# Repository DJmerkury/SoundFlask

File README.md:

# SoundFlask
Eurorack Modular Synthesizer Projects

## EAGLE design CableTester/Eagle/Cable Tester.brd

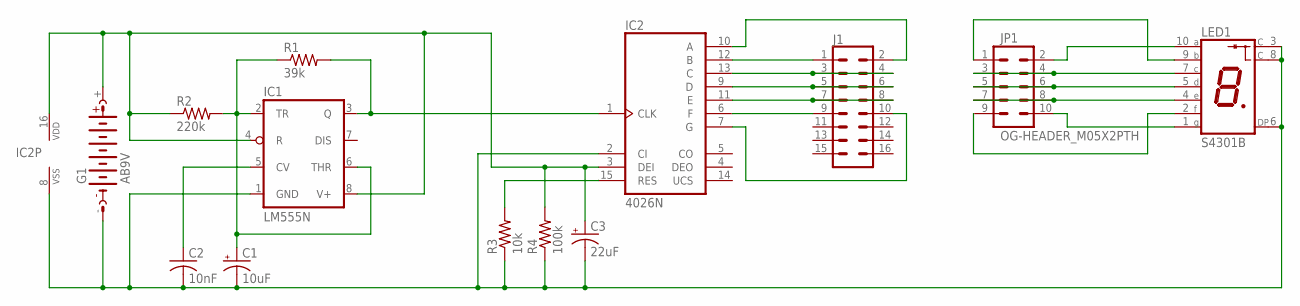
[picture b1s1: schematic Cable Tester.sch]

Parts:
C1: 10uF; RCL_E5-5
C2: 10nF; RCL_C050-055X075
C3: 22uF; RCL_E5-5
G1: AB9V
IC1: LM555N; DIL08
IC2: 4026N; DIL16
J1: CONN_08X2_HEADER; 2X8
JP1: OG-HEADER_M05X2PTH; OG-HEADER_AVR_ICSP
LED1: S4301B
R1: 39k; RESISTOR_0309/10
R2: 220k; RESISTOR_0309/10
R3: 10k; RESISTOR_0309/10
R4: 100k; RESISTOR_0309/10

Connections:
unnamed: C1.+, IC1.2 (TR), IC1.6 (THR), R1.1, R2.2
unnamed: IC1.3 (Q), IC2.1 (CLK), R1.2
unnamed: C2.1, IC1.5 (CV)
unnamed: IC2.15 (RES), R3.2
unnamed: IC2.10 (A), J1.2
unnamed: IC2.12 (B), J1.1
unnamed: IC2.13 (C), J1.3, J1.4
unnamed: IC2.9 (D), J1.5, J1.6
unnamed: IC2.11 (E), J1.7, J1.8
unnamed: IC2.6 (F), J1.9
unnamed: IC2.7 (G), J1.10
unnamed: JP1.2, LED1.10 (A)
unnamed: JP1.1, LED1.9 (B)
unnamed: JP1.3, JP1.4, LED1.7 (C)
unnamed: JP1.5, JP1.6, LED1.5 (D)
unnamed: JP1.7, JP1.8, LED1.4 (E)
unnamed: JP1.10, LED1.1 (G)
unnamed: JP1.9, LED1.2 (F)
unnamed: C3.+, G1.+, IC1.4 (R), IC1.8 (V+), IC2.3 (DEI), IC2.16 (VDD), R2.1, R4.2
unnamed: C1.-, C2.2, C3.-, G1.-, IC1.1 (GND), IC2.2 (CI), IC2.8 (VSS), LED1.3 (C), LED1.6 (DP), LED1.8 (C), R3.1, R4.1

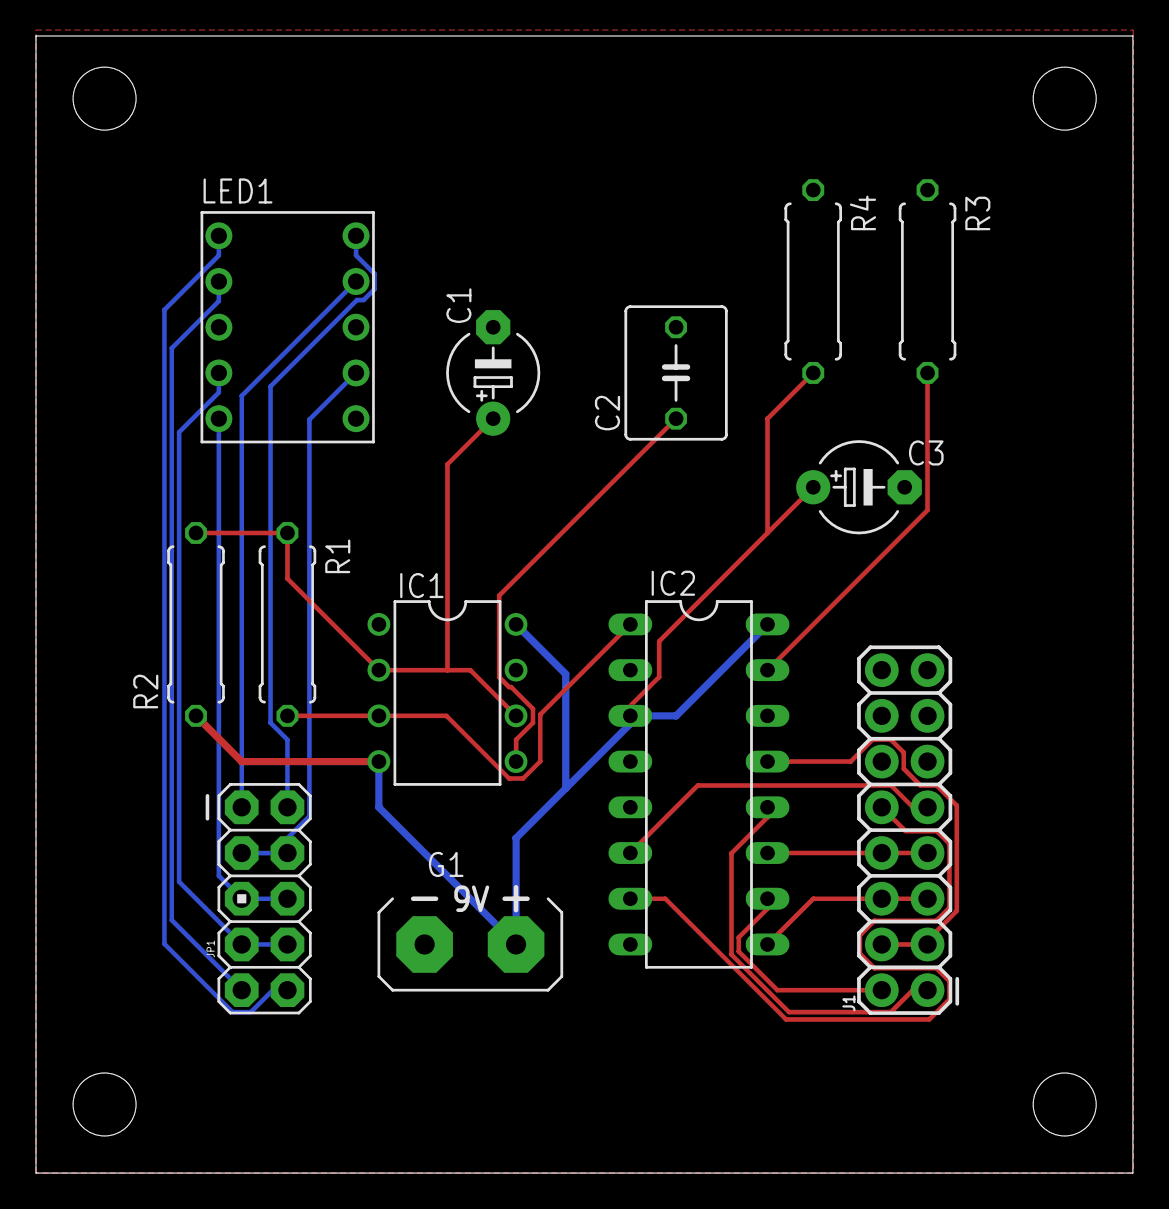
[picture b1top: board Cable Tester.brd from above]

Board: 2 copper layers, 60.9 x 63.2 mm, 13 parts (0 on the bottom side), 20 nets.

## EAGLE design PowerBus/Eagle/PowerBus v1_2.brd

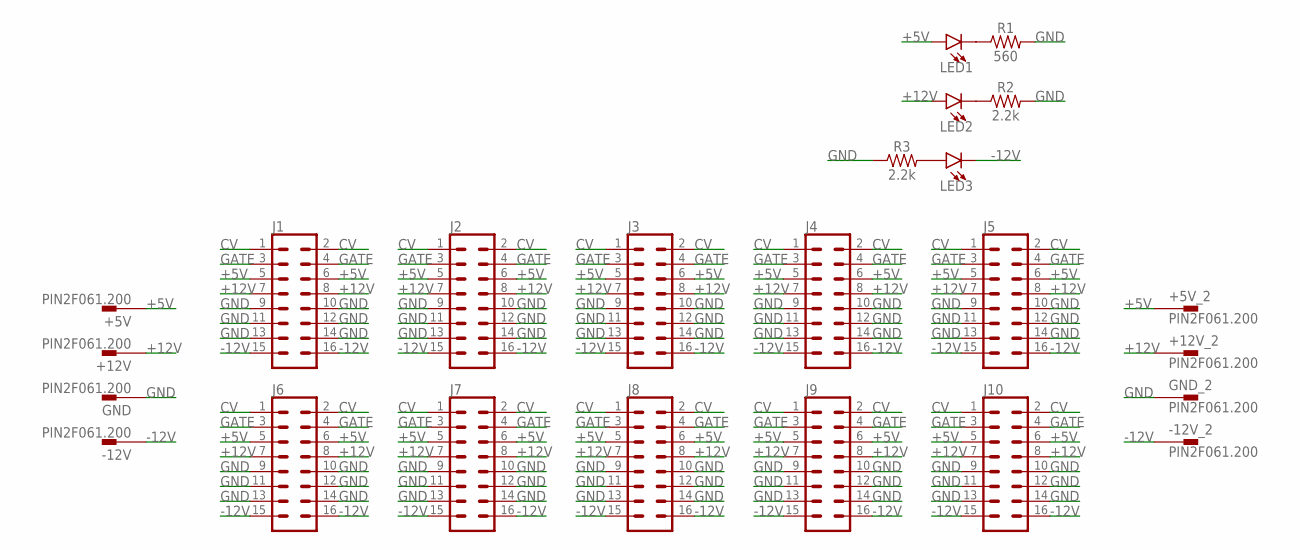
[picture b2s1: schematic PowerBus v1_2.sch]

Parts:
+5V, +5V_2, +12V, +12V_2: PIN2F061.200; F061.200
-12V, -12V_2: PIN2F061.200; F061.200
GND: PIN2F061.200; F061.200
GND_2: PIN2F061.200; F061.200
J1, J2, J3, J4, J5, J6, J7, J8, J9, J10: CONN_08X2_HEADER; 2X8
LED1, LED2, LED3: LED3MM; LED_3MM
R1: 560; AXIAL-0.3
R2, R3: 2.2k; AXIAL-0.3

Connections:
+5V: +5V.1A, +5V.1B, +5V_2.1A, +5V_2.1B, J1.5, J1.6, J2.5, J2.6, J3.5, J3.6, J4.5, J4.6, J5.5, J5.6, J6.5, J6.6, J7.5, J7.6, J8.5, J8.6, J9.5, J9.6, J10.5, J10.6, LED1.A
+12V: +12V.1A, +12V.1B, +12V_2.1A, +12V_2.1B, J1.7, J1.8, J2.7, J2.8, J3.7, J3.8, J4.7, J4.8, J5.7, J5.8, J6.7, J6.8, J7.7, J7.8, J8.7, J8.8, J9.7, J9.8, J10.7, J10.8, LED2.A
-12V: -12V.1A, -12V.1B, -12V_2.1A, -12V_2.1B, J1.15, J1.16, J2.15, J2.16, J3.15, J3.16, J4.15, J4.16, J5.15, J5.16, J6.15, J6.16, J7.15, J7.16, J8.15, J8.16, J9.15, J9.16, J10.15, J10.16, LED3.K (C)
CV: J1.1, J1.2, J2.1, J2.2, J3.1, J3.2, J4.1, J4.2, J5.1, J5.2, J6.1, J6.2, J7.1, J7.2, J8.1, J8.2, J9.1, J9.2, J10.1, J10.2
GATE: J1.3, J1.4, J2.3, J2.4, J3.3, J3.4, J4.3, J4.4, J5.3, J5.4, J6.3, J6.4, J7.3, J7.4, J8.3, J8.4, J9.3, J9.4, J10.3, J10.4
GND: GND.1A, GND.1B, GND_2.1A, GND_2.1B, J1.9, J1.10, J1.11, J1.12, J1.13, J1.14, J2.9, J2.10, J2.11, J2.12, J2.13, J2.14, J3.9, J3.10, J3.11, J3.12, J3.13, J3.14, J4.9, J4.10, J4.11, J4.12, J4.13, J4.14, J5.9, J5.10, J5.11, J5.12, J5.13, J5.14, J6.9, J6.10, J6.11, J6.12, J6.13, J6.14, J7.9, J7.10, J7.11, J7.12, J7.13, J7.14, J8.9, J8.10, J8.11, J8.12, J8.13, J8.14, J9.9, J9.10, J9.11, J9.12, J9.13, J9.14, J10.9, J10.10, J10.11, J10.12, J10.13, J10.14, R1.P$2 (2), R2.P$2 (2), R3.P$1 (1)
unnamed: LED1.K (C), R1.P$1 (1)
unnamed: LED2.K (C), R2.P$1 (1)
unnamed: LED3.A, R3.P$2 (2)

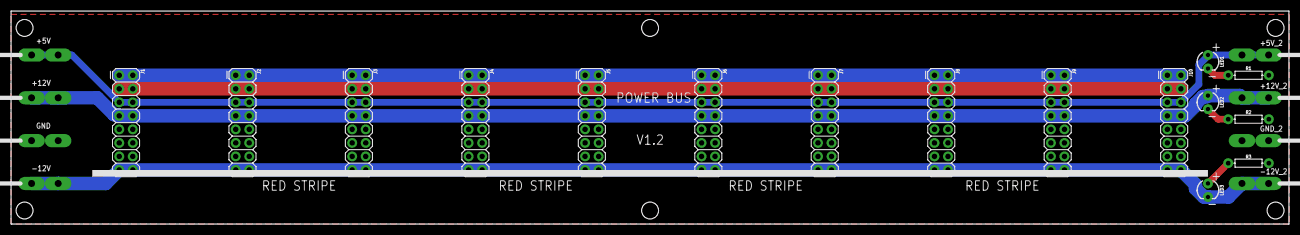
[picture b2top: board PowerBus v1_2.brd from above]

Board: 2 copper layers, 240.0 x 40.0 mm, 24 parts (0 on the bottom side), 9 nets.

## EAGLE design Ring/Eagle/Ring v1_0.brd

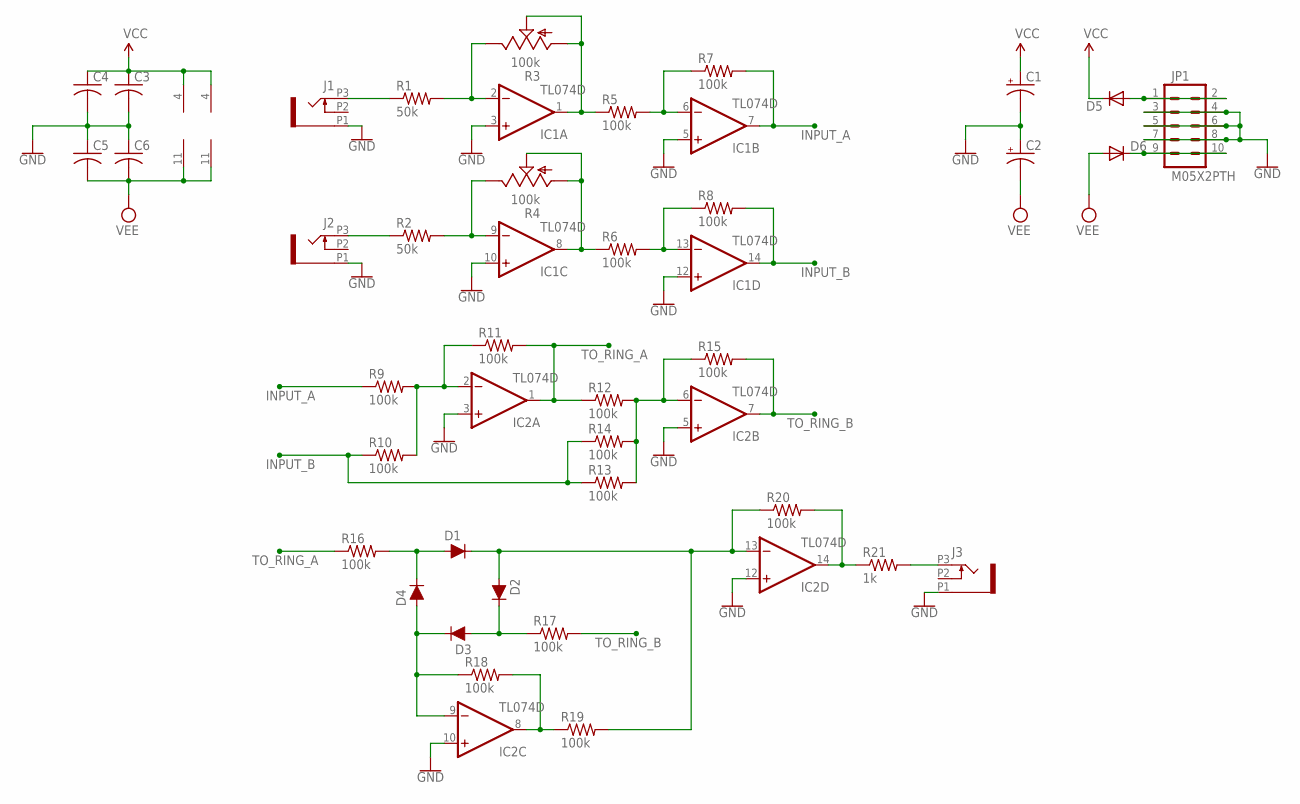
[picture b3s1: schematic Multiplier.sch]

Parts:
C1, C2: RCL_CPOL-USB; RCL_PANASONIC_B
C3, C4, C5, C6: RCL_C-USC0603; RCL_C0603
D1, D2, D3, D4: DIODE-PTH; DIODE-1N4001
D5, D6: DIODE_DIODE-SOD123; DIODE_SOD123
IC1, IC2: TL074D; SO14
J1, J2, J3: OG-PJ301_PJ301_THONKICONN8; OG-PJ301_WQP_PJ_301M8
JP1: M05X2PTH; OG-HEADER_AVR_ICSP
R1, R2: 50k; RESISTOR_R0603
R3, R4: 100k; POT-ALPS_ALPS_POT_VERTICAL_PS2
R5, R6, R7, R8, R9, R10, R11, R12, R13, R14, R15, R16, R17, R18, R19, R20: 100k; RESISTOR_R0603
R21: 1k; RESISTOR_R0603

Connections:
GND: C1.-, C2.+, C3.2, C4.2, C5.1, C6.1, IC1.3 (+IN), IC1.5 (+IN), IC1.10 (+IN), IC1.12 (+IN), IC2.3 (+IN), IC2.5 (+IN), IC2.10 (+IN), IC2.12 (+IN), J1.P1 (1), J2.P1 (1), J3.P1 (1), JP1.3, JP1.4, JP1.5, JP1.6, JP1.7, JP1.8
INPUT_A: IC1.7 (OUT), R7.2, R9.1
INPUT_B: IC1.14 (OUT), R8.2, R10.1, R13.1, R14.1
unnamed: J1.P3 (3), R1.1
unnamed: J2.P3 (3), R2.1
unnamed: IC1.9 (-IN), R2.2, R4.P$1 (E)
unnamed: IC1.2 (-IN), R1.2, R3.P$1 (E)
unnamed: IC1.1 (OUT), R3.P$2 (S), R3.P$3 (A), R5.1
unnamed: IC1.8 (OUT), R4.P$2 (S), R4.P$3 (A), R6.1
unnamed: IC2.2 (-IN), R9.2, R10.2, R11.1
unnamed: IC1.6 (-IN), R5.2, R7.1
unnamed: IC1.13 (-IN), R6.2, R8.1
unnamed: D1.A, D4.C, R16.2
unnamed: IC2.6 (-IN), R12.2, R13.2, R14.2, R15.1
unnamed: D1.C, D2.A, IC2.13 (-IN), R19.2, R20.1
unnamed: D2.C, D3.A, R17.1
unnamed: D3.C, D4.A, IC2.9 (-IN), R18.1
unnamed: IC2.8 (OUT), R18.2, R19.1
unnamed: IC2.14 (OUT), R20.2, R21.1
unnamed: J3.P3 (3), R21.2
unnamed: D5.A, JP1.1, JP1.2
unnamed: D6.C, JP1.9, JP1.10
TO_RING_A: IC2.1 (OUT), R11.2, R12.1, R16.1
TO_RING_B: IC2.7 (OUT), R15.2, R17.2
VCC: C1.+, C3.1, C4.1, D5.C, IC1.4 (V+), IC2.4 (V+)
VEE: C2.-, C5.2, C6.2, D6.A, IC1.11 (V-), IC2.11 (V-)

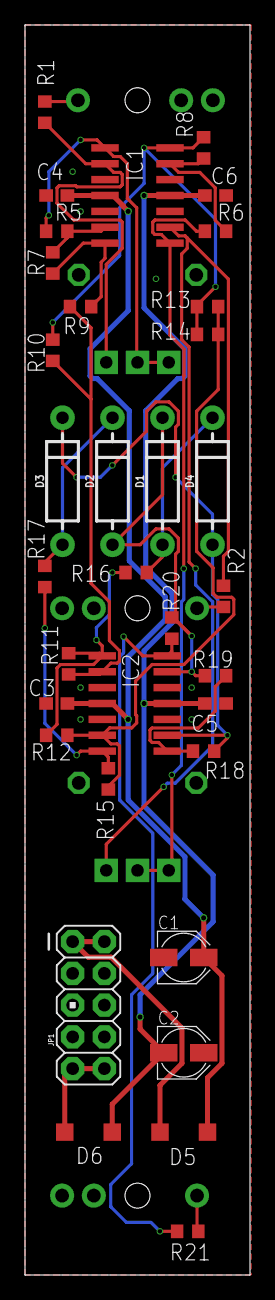
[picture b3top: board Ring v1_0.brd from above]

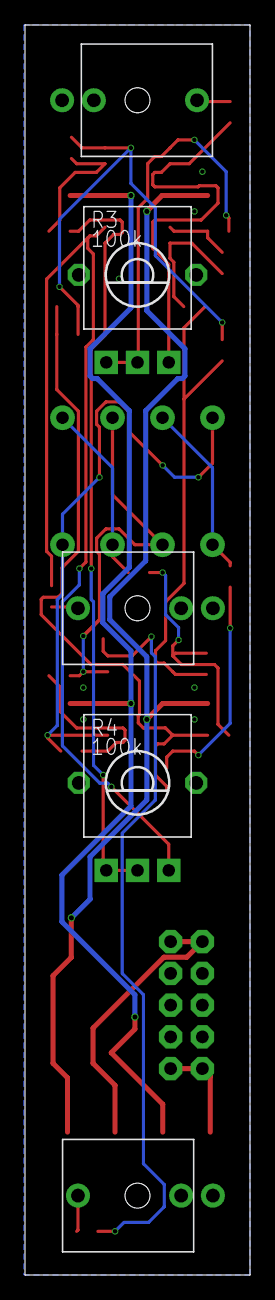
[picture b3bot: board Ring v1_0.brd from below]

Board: 2 copper layers, 18.0 x 100.0 mm, 39 parts (5 on the bottom side), 26 nets.

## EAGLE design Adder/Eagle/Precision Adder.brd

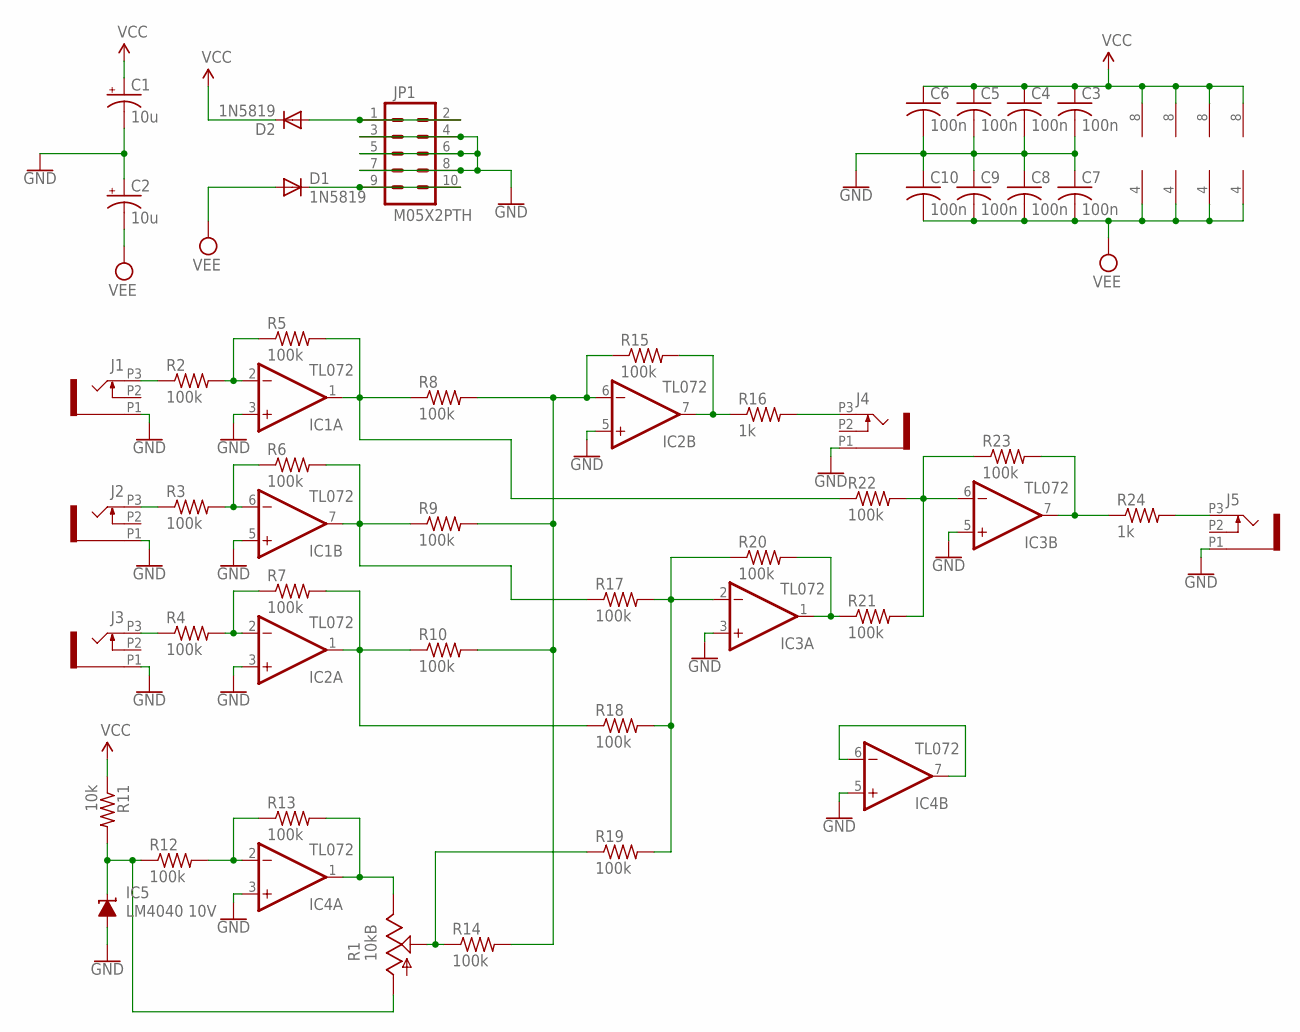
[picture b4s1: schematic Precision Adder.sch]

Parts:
C1, C2: 10u; RCL_PANASONIC_B
C3, C4, C5, C6, C7, C8, C9, C10: 100n; RCL_C0603
D1, D2: 1N5819; DIODE_SOD123
IC1, IC2, IC3, IC4: TL072; GM-ICS_SO08
IC5: LM4040 10V; TEXAS_DBZ_R-PDSO-G3
J1, J2, J3, J4, J5: OG-PJ301_PJ301_THONKICONN6; OG-PJ301_WQP_PJ_301M6
JP1: M05X2PTH; OG-HEADER_AVR_ICSP
R1: 10kB; POT-ALPS_ALPS_POT_VERTICAL_PS
R2, R3, R4, R5, R6, R7, R8, R9, R10, R12, R13, R14, R15, R17, R18, R19, R20, R21, R22, R23: 100k; RESISTOR_R0603
R11: 10k; RESISTOR_R0603
R16, R24: 1k; RESISTOR_R0603

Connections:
GND: C1.-, C2.+, C3.2, C4.2, C5.2, C6.2, C7.1, C8.1, C9.1, C10.1, IC1.3 (+IN), IC1.5 (+IN), IC2.3 (+IN), IC2.5 (+IN), IC3.3 (+IN), IC3.5 (+IN), IC4.3 (+IN), IC4.5 (+IN), IC5.2 (A), J1.P1 (1), J2.P1 (1), J3.P1 (1), J4.P1 (1), J5.P1 (1), JP1.3, JP1.4, JP1.5, JP1.6, JP1.7, JP1.8
unnamed: D2.A, JP1.1, JP1.2
unnamed: J1.P3 (3), R2.1
unnamed: IC1.2 (-IN), R2.2, R5.1
unnamed: IC1.1 (OUT), R5.2, R8.1, R22.1
unnamed: D1.C, JP1.9, JP1.10
unnamed: J2.P3 (3), R3.1
unnamed: IC1.6 (-IN), R3.2, R6.1
unnamed: IC1.7 (OUT), R6.2, R9.1, R17.1
unnamed: IC2.1 (OUT), R7.2, R10.1, R18.1
unnamed: IC2.2 (-IN), R4.2, R7.1
unnamed: J3.P3 (3), R4.1
unnamed: IC5.1 (C), R1.P$3 (A), R11.2, R12.1
unnamed: IC4.2 (-IN), R12.2, R13.1
unnamed: IC4.1 (OUT), R1.P$1 (E), R13.2
unnamed: IC4.6 (-IN), IC4.7 (OUT)
unnamed: IC2.6 (-IN), R8.2, R9.2, R10.2, R14.2, R15.1
unnamed: R1.P$2 (S), R14.1, R19.1
unnamed: IC2.7 (OUT), R15.2, R16.1
unnamed: J4.P3 (3), R16.2
unnamed: IC3.2 (-IN), R17.2, R18.2, R19.2, R20.1
unnamed: IC3.1 (OUT), R20.2, R21.1
unnamed: IC3.6 (-IN), R21.2, R22.2, R23.1
unnamed: IC3.7 (OUT), R23.2, R24.1
unnamed: J5.P3 (3), R24.2
VCC: C1.+, C3.1, C4.1, C5.1, C6.1, D2.C, IC1.8 (V+), IC2.8 (V+), IC3.8 (V+), IC4.8 (V+), R11.1
VEE: C2.-, C7.2, C8.2, C9.2, C10.2, D1.A, IC1.4 (V-), IC2.4 (V-), IC3.4 (V-), IC4.4 (V-)

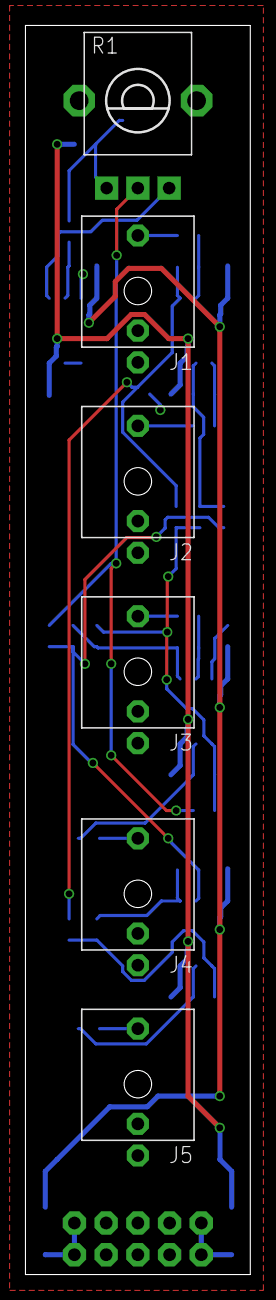
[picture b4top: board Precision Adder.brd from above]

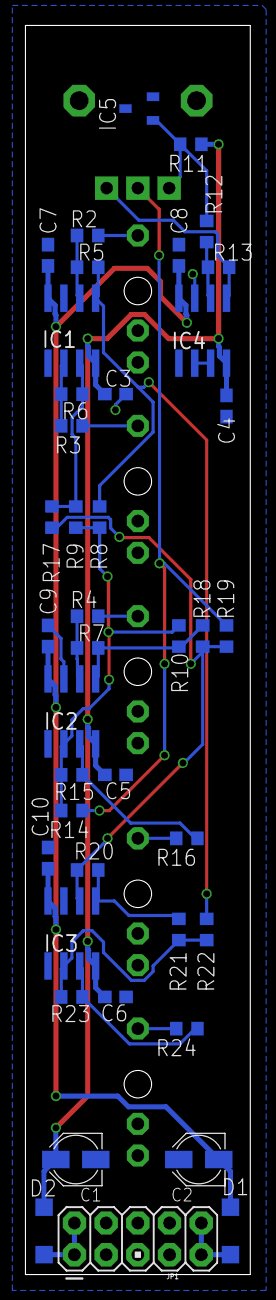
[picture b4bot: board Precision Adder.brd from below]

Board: 2 copper layers, 18.0 x 100.0 mm, 47 parts (41 on the bottom side), 27 nets.

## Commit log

2020-07-25 Create Power Bus
2020-07-25 Rename Power Bus.brd to Power Bus/Eagle/Power Bus.brd
2020-07-25 Rename Power Bus.sch to Power Bus/Eagle/Power Bus.sch
2020-07-30 Create delete
2020-07-30 Rename Precision Adder.sch to Adder/Eagle/Precision Adder.sch
2020-08-10 Create New
2020-08-12 Rename Power Bus/Eagle/Power Bus.sch to PowerBus/Eagle/PowerBus v1_2.sch
2020-08-12 Rename Power Bus/Eagle/Power Bus.brd to PowerBus/Eagle/PowerBus v1_2.brd
2020-08-12 Rename PowerBus v1_2 Build Note.txt to Build Note - PowerBus v1_2.txt
2020-08-12 Rename Multiplier.brd to Ring v1_0.brd
2020-08-12 Rename Multiplier.sch to Ring v1_0.sch
2020-08-20 Create This Project Has Not Been Built Yet
2020-08-23 Create Modifications
2021-01-02 Create Initial Commit
2021-01-31 Rename Build Note - Bunsen v1_0.txt to Build Note - Bunsen - Rev 1_0.txt
2021-01-31 Rename Build Note - Pipet v1_0.txt to Build Note - Pipet - Rev 1_0.txt
